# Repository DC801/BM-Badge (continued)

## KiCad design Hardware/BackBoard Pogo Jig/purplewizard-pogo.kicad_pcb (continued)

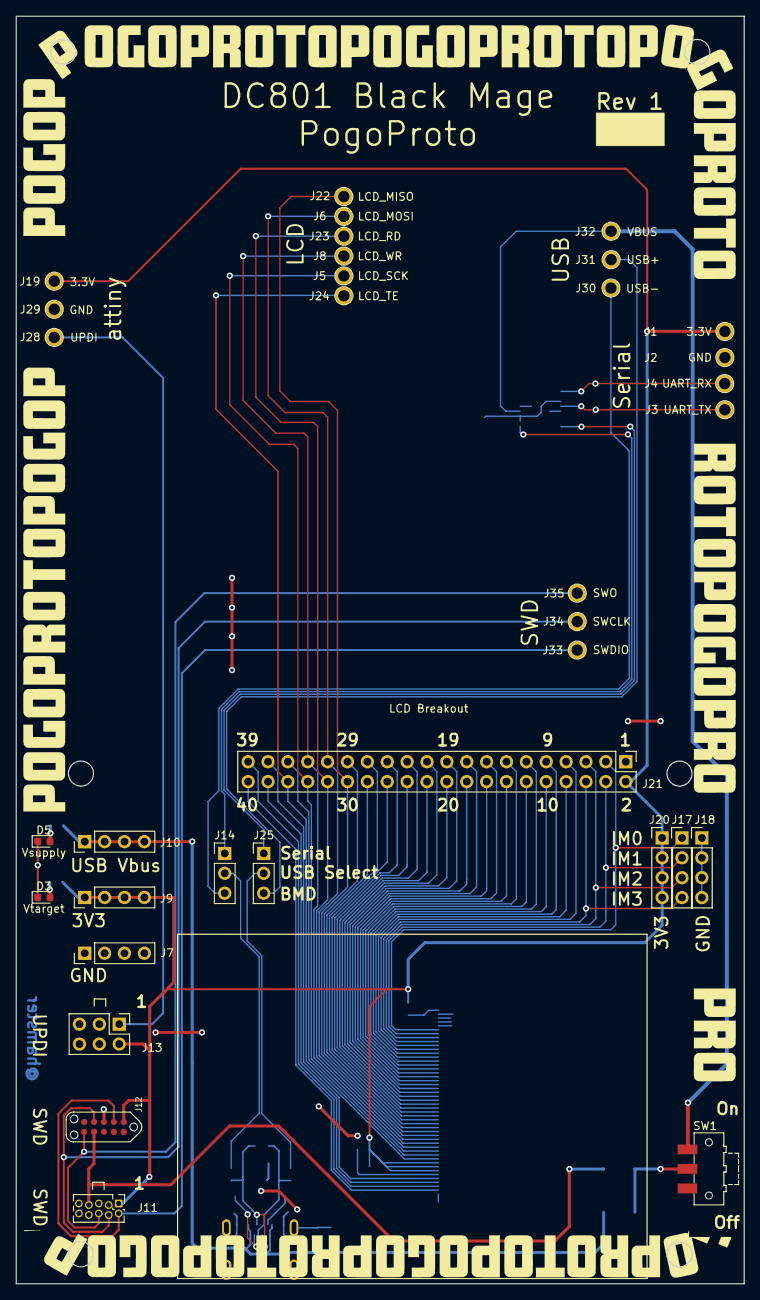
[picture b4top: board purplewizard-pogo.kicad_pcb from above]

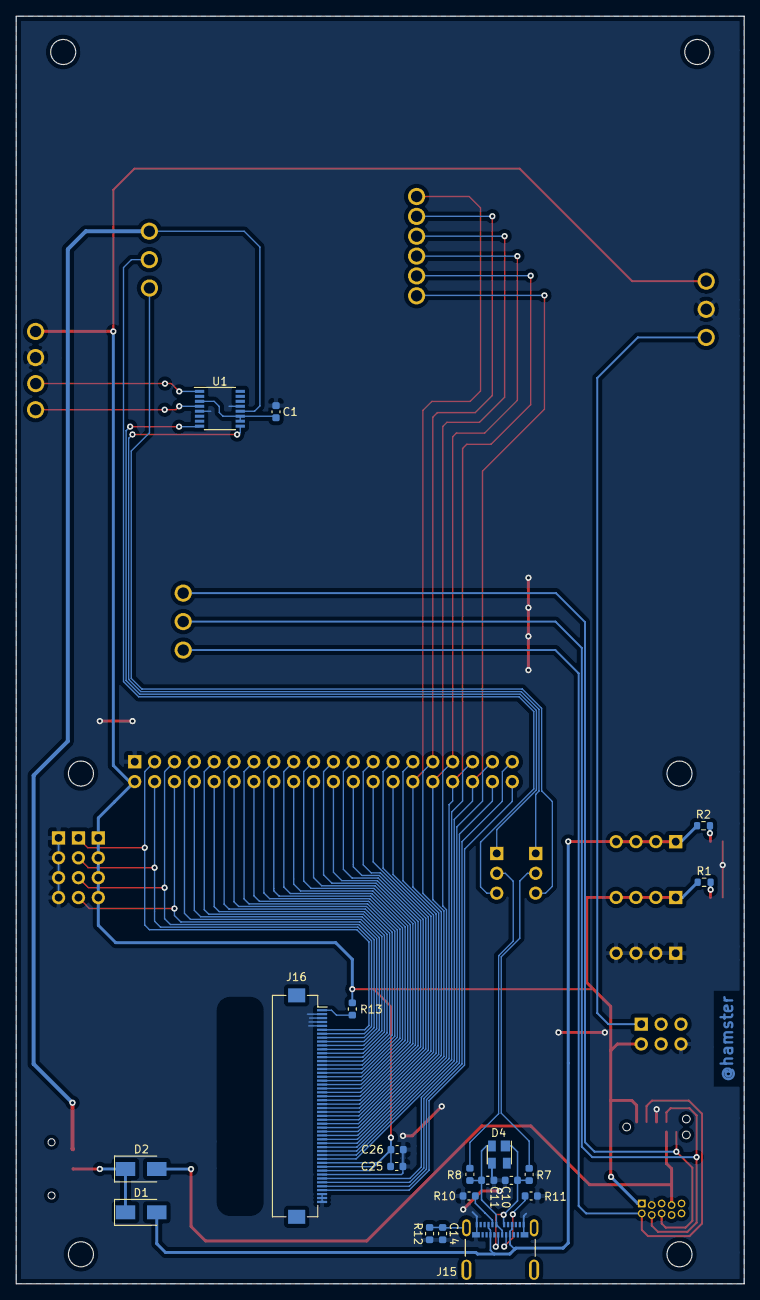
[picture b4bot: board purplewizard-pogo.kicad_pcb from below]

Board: 2 copper layers, 93.0 x 162.0 mm, 54 parts (20 on the bottom side), 65 nets.

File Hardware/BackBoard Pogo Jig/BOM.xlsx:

Ref Des | Description | Mfg Part # | Package | Supplier | Supplier Part # | QTY per badge | Cost ea | Cost badge
C1,C15,C25 | 0.1uF Cap |  | 0603 | Digikey | 478-06036C104KAT4ACT-ND | 3 | 1.78E-2 | 5.3400000000000003E-2
C10,C11 | 47pF Cap |  | 0603 | Digikey | 732-7750-1-ND | 2 | 2.3199999999999998E-2 | 4.6399999999999997E-2
C26 | 10uF cap |  | 0603 | Digikey | 587-6017-1-ND | 1 | 6.4399999999999999E-2 | 6.4399999999999999E-2
D1,D2 | Schottky diode | VS-10MQ040-M3/5AT |  | Digikey | 112-VS-10MQ040-M3/5ATDKR-ND | 2 | 0.12972 | 0.25944
D3,D5 | LEDs |  | 0603 | Digikey | 160-1435-1-ND | 2 | 8.4599999999999995E-2 | 0.16919999999999999
D4 | TVS Diode | SP0503BAHTG | SOT-143-4 | Digikey | F2715DKR-ND | 1 | 0.4622 | 0.4622
DNS | 2.4" TFT 320x240 LCD display |  |  | buydisplay | https://www.buydisplay.com/color-2-4-inch-tft-lcd-module-dis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 | 1 | 4.82 | 4.82
J15 | USB-C | 1054500101 |  | Digikey | WM12856CT-ND | 1 | 1.8717999999999999 | 1.8717999999999999
J16 | FPC connector | 62684-50210E9ALF | Top Contact, 50 pin | Digikey | 609-5388-1-ND | 1 | 0.82450000000000001 | 0.82450000000000001
R12 | 10k Resistor |  | 0603 | Digikey | RMCF0603JT10K0CT-ND | 2 | 5.5999999999999999E-3 | 1.12E-2
R10,R11 | 5.1k Resistor |  | 0603 | Digikey | RMCF0603JG5K10CT-ND | 2 |  | 0
R13 | 33R Resistor |  |  | Digikey | RMCF0603JT33R0CT-ND | 1 | 5.5999999999999999E-3 | 5.5999999999999999E-3
R1,R2 | 470R Resistor |  | 0603 | Digikey | RMCF0603JT470RCT-ND | 2 | 5.5999999999999999E-3 | 1.12E-2
R7,R8 | 27R Resistor |  | 0603 | Digikey | RMCF0603JT27R0CT-ND | 2 | 5.5999999999999999E-3 | 1.12E-2
SW1 | Power switch | JS102011SAQN |  | Digikey | 401-1999-1-ND | 1 | 0.50907999999999998 | 0.50907999999999998
J1, J19, J2, J22, J23, J24, J28, J29, J3, J30, J31, J32, J33, J34, J35, J4, J5,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 | Pogo Socket |  |  | Digikey | ED1012-ND | 19
 |  |  |  |  |  | Total Parts |  | Cost Per
 |  |  |  |  |  | 38 |  | 9.0198200000000028

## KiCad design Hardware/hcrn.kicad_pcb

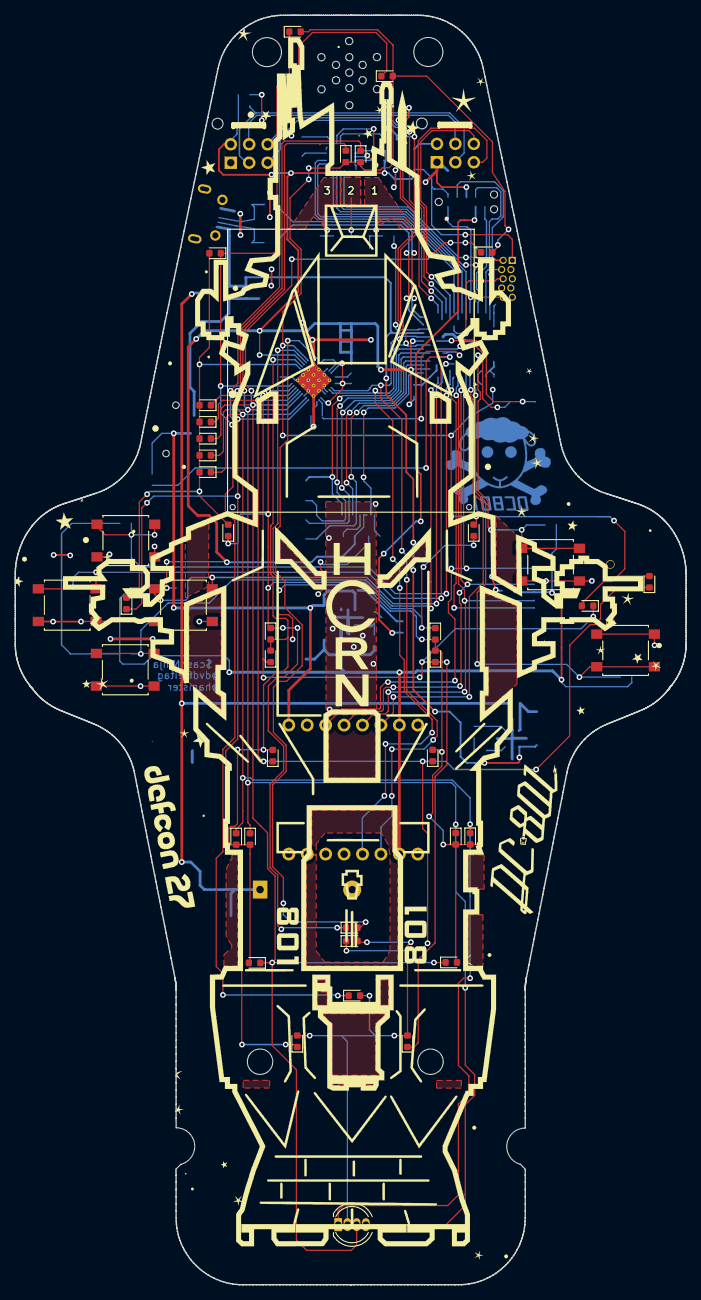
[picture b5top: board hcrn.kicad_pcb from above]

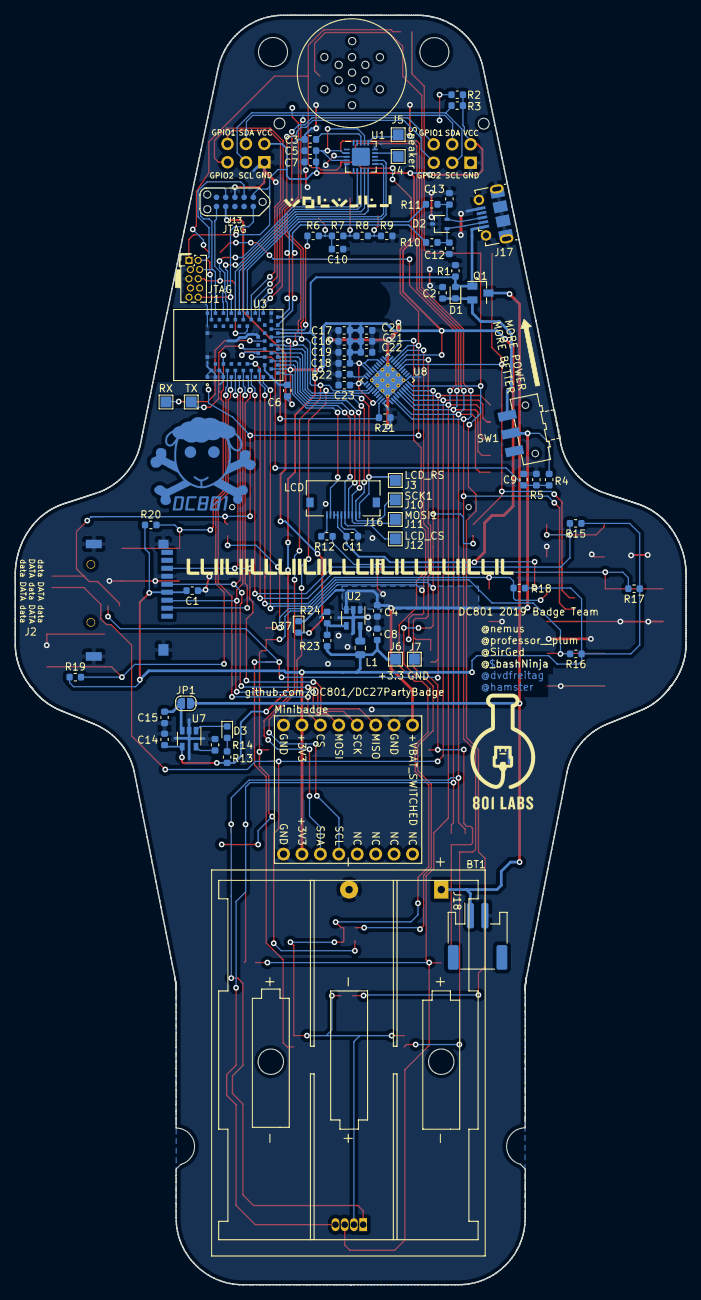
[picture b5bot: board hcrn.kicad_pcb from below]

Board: 2 copper layers, 92.5 x 175.0 mm, 120 parts (77 on the bottom side), 76 nets.

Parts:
BT1: Battery; BatteryHolder_Keystone_2479_3xAAA
C1, C2, C10, C11, C16, C18, C21: 0.1uF; C_0603_1608Metric
C3, C4, C5, C6, C7, C14, C15: 4.7uF; C_0603_1608Metric
C8, C20: 22uF; C_0603_1608Metric
C9: 1nF; C_0603_1608Metric
C12, C13: 47pF; C_0603_1608Metric
C17, C19, C22, C23: 0.47uF; C_0603_1608Metric
D1, D37: D_Schottky; D_0603_1608Metric
D2: SP0503BAHT; SOT-323_SC-70
D3: RED; LED_0603_1608Metric
D4, D5, D6, D7, D8, D9, D10, D11, D12, D13, D14, D15, D16, D17, D18, D19, D20, D21, D22, D23, D24, D25, D26, D27, D28, D29, D30, D31, D32, D33, D34, D35, D36: LED; LED_0603_1608Metric
D38: LED_ARGB; LED_D5.0mm-4_RGB
J1: JTAG; PinHeader_2x05_P1.27mm_Vertical_Sneaky
J2: Micro_SD_Card_SPI; MicroSD-Socket-Seeed-320090008
J3: LCD_RS; TestPoint_Pad_1.5x1.5mm
J4: SPKR+; TestPoint_Pad_1.5x1.5mm
J5: SPKR-; TestPoint_Pad_1.5x1.5mm
J6: 3.3V; TestPoint_Pad_1.5x1.5mm
J7: GND; TestPoint_Pad_1.5x1.5mm
J8: UART_TX; TestPoint_Pad_1.5x1.5mm
J9: UART_RX; TestPoint_Pad_1.5x1.5mm
J10: SCK1; TestPoint_Pad_1.5x1.5mm
J11: MOSI1; TestPoint_Pad_1.5x1.5mm
J12: LCD_CS; TestPoint_Pad_1.5x1.5mm
J13: TagConnect; TC2050-NL_SMALL
J16: LCD; XF2L-1035-1A
J17: USB_B_Micro; USB_Micro-B_Molex-105017-0001
J18: Battery; JST_PH_S2B-PH-SM4-TB_1x02-1MP_P2.00mm_Horizontal
JP1: LiPo Charger Enable; SolderJumper-2_P1.3mm_Open_RoundedPad1.0x1.5mm
L1: 4.7uH; L_0805_2012Metric
Q1: FDN360P; SuperSOT-3
R1, R7, R15, R16, R17, R18, R19, R20: 10k; R_0603_1608Metric
R2, R3: 4.7k; R_0603_1608Metric
R4: 806k; R_0603_1608Metric
R5: 2M; R_0603_1608Metric
R6: 3.9k; R_0603_1608Metric
R8: 15k; R_0603_1608Metric
R9: 4.99k; R_0603_1608Metric
R10, R11: 27R; R_0603_1608Metric
R12: 33R; R_0603_1608Metric
R13: 470R; R_0603_1608Metric
R14: 2.0k; R_0603_1608Metric
R21: 100k; R_0603_1608Metric
R22: 20k; R_0603_1608Metric
R23: 536k; R_0603_1608Metric
R24: 118k; R_0603_1608Metric
SW1: Power; SW_SPDT_CK-JS102011SAQN
SW2, SW3, SW4, SW5, SW6, SW7: SW_Push; SW_SPST_B3S-1000
U1: NAU8810; QFN-20-1EP_4x4mm_P0.5mm_EP2.5x2.5mm
U2: PAM2305DABADJ; SOT-23-5
U3: BMD-340; RIGADO_BMD-340
U4: Minibadge 1; SAINTCON-Minibadge-BackSilk
U5, U6: SHITTY_ADDON; Badgelife-SAOv169-BADGE-2x3-NoOutline
U7: MCP73832-2-OT; SOT-23-5
U8: IS31FL3736; QFN-40-1EP_5x5mm_P0.4mm_EP3.6x3.6mm_ThermalVias

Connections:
+3V3: C1.2, C5.2, C6.1, C7.2, C8.1, C11.2, C16.1, C17.2, C18.1, C19.2, C20.1, C21.1, C22.2, C23.1, J1.1, J2.4, J6.1, J13.1, J16.7, J16.8, L1.2, R2.2, R3.2, R15.1, R16.1, R17.1, R18.1, R19.1, R20.1, R23.2, U1.2, U1.4, U1.17, U3.17, U3.65, U4.7, U4.15, U5.1, U6.1, U8.17, U8.23, U8.27, U8.28, U8.31, U8.38
+BATT: BT1.1, J18.1, JP1.2, Q1.3
+BATT_SW: C4.1, D37.1, R4.2, R12.1, SW1.2, U2.1, U2.3, U4.1
/EE_Level1: C10.2, R6.2, R7.1
/EE_Level2: R7.2, R8.1
/EE_Level3: R8.2, R9.1
/USB+: R11.2, U3.68
/USB-: R10.2, U3.67
BUTTON_A: R19.2, SW6.1, U3.6
BUTTON_B: R20.2, SW7.1, U3.49
BUTTON_DOWN: R16.2, SW3.1, U3.15
BUTTON_LEFT: R17.2, SW4.1, U3.52
BUTTON_RIGHT: R18.2, SW5.1, U3.14
BUTTON_UP: R15.2, SW2.1, U3.12
EEPuzzle: R6.1, U3.27
GND: BT1.2, C1.1, C2.2, C3.1, C4.2, C5.1, C6.2, C7.1, C8.2, C9.2, C10.1, C11.1, C12.1, C13.2, C14.1, C15.1, C16.2, C17.1, C18.2, C19.1, C20.2, C21.2, C22.1, C23.2, D2.3, J1.3, J1.5, J2.6, J2.10, J7.1, J13.3, J16.6, J17.5, J17.6, J18.2, R1.1, R5.1, R9.2, R14.1, R21.1, R22.1, R24.1, SW2.2, SW3.2, SW4.2, SW5.2, SW6.2, SW7.2, U1.3, U1.5, U1.15, U2.2, U3.1, U3.2, U3.3, U3.4, U3.5, U3.16, U3.18, U3.29, U3.30, U3.45, U3.46, U3.47, U3.55, U4.2, U4.8, U4.16, U5.2, U6.2, U7.2, U8.4, U8.11, U8.26, U8.35, U8.36, U8.40, U8.41
I2S_LRCK: U1.8, U3.40
I2S_MCK: U1.10, U3.37
I2S_SCK: U1.9, U3.38
I2S_SCL: U1.11, U3.36
I2S_SDA: U1.12, U3.35
I2S_SDOUT: U1.7, U3.41
LCD_CS: J12.1, J16.5, U3.62
LCD_LED: J16.9, U3.61
LCD_RESET: J16.4, U3.19
LCD_RS: J3.1, J16.1, U3.64
LED_RESET: R21.2, U3.53, U8.39
MINI_CS: U3.7, U4.6
MISO0: J2.7, U3.8, U4.3
MOSI0: J2.3, U3.10, U4.5
MOSI1: J11.1, J16.3, U3.63
unnamed: C2.1, D1.1, Q1.2, SW1.3
unnamed: C3.2, U1.18
unnamed: C12.2, D2.1, J17.2, R10.1
unnamed: C13.1, D2.2, J17.3, R11.1
unnamed: C15.2, JP1.1, U7.3
unnamed: D3.1, U7.1
unnamed: D3.2, R13.2
unnamed: D10.1, D18.1, D34.1, U8.2
unnamed: D4.2, D5.2, D6.2, D7.2, D8.2, D9.2, D10.2, D11.2, U8.15
unnamed: D11.1, D35.1, D36.1, U8.10
unnamed: D4.1, D12.1, D19.1, D20.1, D28.1, U8.9
unnamed: D12.2, D13.2, D14.2, D15.2, D16.2, D17.2, U8.16
unnamed: D5.1, D13.1, D21.1, D26.1, D29.1, U8.8
unnamed: D6.1, D14.1, D22.1, D27.1, D30.1, U8.7
unnamed: D7.1, D15.1, D23.1, D31.1, D38.3, U8.6
unnamed: D8.1, D16.1, D24.1, D32.1, D38.4, U8.5
unnamed: D9.1, D17.1, D25.1, D33.1, D38.1, U8.3
unnamed: D18.2, D19.2, D26.2, D27.2, D36.2, D38.2, U8.21
unnamed: D20.2, D21.2, D22.2, D23.2, D24.2, D25.2, U8.18
unnamed: D28.2, D29.2, D30.2, D31.2, D32.2, D33.2, D34.2, D35.2, U8.19
unnamed: J4.1, U1.14
unnamed: J5.1, U1.16
unnamed: J16.10, R12.2
unnamed: L1.1, U2.5
unnamed: R14.2, U7.5
unnamed: R22.2, U8.30
unnamed: R23.1, R24.2, U2.4
S1_1: U3.31, U5.5
S1_2: U3.32, U5.6
S2_1: U3.34, U6.5
S2_2: U3.33, U6.6
SCK0: J2.5, U3.9, U4.4
SCK1: J10.1, J16.2, U3.21
SCL: R3.1, U3.23, U4.13, U5.4, U6.4, U8.34
SDA: R2.1, U3.25, U4.14, U5.3, U6.3, U8.33
SD_CS: J2.2, U3.11
SW0: J1.6, J13.6, U3.56
SWCLK: J1.4, J13.4, U3.43
SWDIO: J1.2, J13.2, U3.44
TC_PWR: D37.2, J13.7
UART_RX: J9.1, U3.24
UART_TX: J8.1, U3.22
VBAT_SENSE: C9.1, R4.1, R5.2, U3.20
VBUS: C14.2, D1.2, J17.1, Q1.1, R1.2, R13.1, U3.66, U7.4
nRESET: J1.10, J13.10, U3.39

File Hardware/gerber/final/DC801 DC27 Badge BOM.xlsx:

Refdes | Manufacturer | Part Number | Description | Package | Supplier | Supplier Part | Cost Each (assumes 100 unit pricing) | Qty per board | Stuff? | QOH | Needed | To Order | Cost Per Board | Qty ordered | Actual Cost | Datasheet
LiPo Charger |  |  |  |  |  |  |  |  |  |  | 10.0
D3 |  |  | Red LED, LiPo Charger | 0603 |  |  |  | 1.0 | N |  | 10
C14,C15 |  |  | 4.7uF, LiPo Charger | 0603 |  |  |  | 2.0 | N |  | 20
R14 |  |  | 2k ohm, LiPo Charger | 0603 |  |  |  | 1.0 | N |  | 10
R13 |  |  | 470 ohm, LiPo Charger | 0603 |  |  |  | 1.0 | N |  | 10
U7 | Microchip | MCP73832-2-OT | LiPo charger | SOT-23-5 |  |  |  | 1.0 | N |  | 10 |  |  |  |  | https://www.microchip.com/wwwproducts/en/MCP73832
J18 | JST | S2B-PH-SM4-TB(LF)(SN) | JST 2 pin |  | Digikey | 455-1749-1-ND |  | 1.0 |  | 50.0 | 10 | 0.0
Non-stuff, virtual |  |  |  |  |  |  |  |  |  |  | 0
J1 |  |  | JTAG | 2x5, 1.27mm |  |  |  |  | N |  | 0
J12 |  |  | JTAG | TC2050
J4-12 |  |  | Test point |  |  |  |  |  | N |  | 0
JP1 |  |  | Jumper pad |  |  |  |  |  | N |  | 0
U4 |  |  | Minibadge socket |  |  |  |  |  | N |  | 0
U5,U6 |  |  | Shitty addon |  |  |  |  |  | N |  | 0
Solder later |  |  |  |  |  |  |  |  |  |  | 0
BT1 | Keystone | 2479.0 | 3xAAA |  | Digikey | 36-2479-ND |  |  |  | 0.0 | 0
Speaker |  | SP-1504 | 8 ohm speaker |  | Digikey | 433-1106-ND |  |  |  | 0.0 | 0
D38 |  |  | RGB LED | RGB Through Hole | https://www.aliexpress.com/item/Free-shipping-100pcs-lot-5mm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 |  |  | 1.0 |  | 0.0 | 10 | 100.0
 |  |  |  |  |  |  |  |  |  |  | 0
Parts to stuff at board house |  |  |  |  |  |  |  |  |  |  | 0
C1,C2,C10,C11,C16,C18,C21 |  |  | 0.1uF 5v | 0603 | https://www.arrow.com/en/products/cl10b104kb8nnnc/samsung-el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 |  |  | 7.0 |  | 0.0 | 70 | 100.0
C3,C4,C5,C6,C7,C14,C15 |  |  | 4.7uF 5v | 0603 | https://www.arrow.com/en/products/cl10a475kp8nnnc/samsung-el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 |  |  | 7.0 |  | 50.0 | 70 | 100.0
C8,C20 |  |  | 22uF | 0603 | https://www.arrow.com/en/products/grm188r60j226me15d/murata-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 |  |  | 2.0 |  | 0.0 | 20 | 100.0
C9 |  |  | 1nF | 0603 | https://www.arrow.com/en/products/cl10b102mb8nnnc/samsung-el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 |  |  | 1.0 |  | 0.0 | 10 | 100.0
C12,C13 |  |  | 47pF | 0603 | https://www.arrow.com/en/products/cl10c470jb8nnnd/samsung-el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 |  |  | 2.0 |  | 0.0 | 20 | 100.0
C17,C19,C22,C23 |  |  | 0.47uF | 0603 | https://www.arrow.com/en/products/cl10b474kp8nnnc/samsung-el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 |  |  | 4.0 |  | 0.0 | 40 | 100.0
D1.D37 |  |  | Schottky | SOT-143 |  |  |  | 1.0 |  | 25.0 | 10 | 0.0
D2 | Littel Fuse | SP0503BAHT | TVS diode | SOT-143 | https://www.arrow.com/en/products/sp0503bahtg/littelfuse |  |  | 1.0 |  | 0.0 | 10 | 100.0
D30 |  |  | LED, white |  |  |  |  | 1.0 |  | 0.0 | 10 | 100.0
D33,D13,D21,D17,D25,D19,D36 |  |  | LED, purple |  |  |  |  | 7.0 |  | 0.0 | 70 | 100.0
D32,D10,D4,D28,D12,D20,D29,D14,D22,D16,D24,D15,D23,D27,D18,D26 |  |  | LED, amber |  |  |  |  | 16.0 |  | 0.0 | 160 | 250.0
D5,D6,D7,D8,D9,D11,D31,D34,D35 |  |  | LED, red | 0603 |  |  |  | 9.0 |  | 0.0 | 90 | 100.0
J2 | Schenzen Best | TF-01 | Micro SD Card Socket |  | https://www.aliexpress.com/item/10Pcs-TransFlash-TF-Micro-Me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 |  |  | 1.0 |  | 0.0 | 10 | 0.0 |  |  |  | https://statics3.seeedstudio.com/images/opl/datasheet/320090008.pdf
J16 |  | XF2L-1035-1A | FFC/FPC LCD connector |  | Digikey | Z5306CT-ND |  | 1.0 |  | 30.0 | 10 | 0.0
J17 | Molex | 105017-0001 | USB Micro B, 'with holes' |  | Digikey | WM1399CT-ND |  | 1.0 |  | 25.0 | 10 | 0.0
L1 |  |  | 4.7uH | 0805 | https://www.arrow.com/en/products/aiml-0805hc-4r7m-t/abracon |  |  | 1.0 |  | 0.0 | 10 | 100.0
Q1 | On Semi | FDN360P | P-Mosfet | SuperSOT-3 | Mouser | 512-FDN360P |  | 1.0 |  | 30.0 | 10 | 0.0
R1,R7,R15,R16,R17,R18,R19,R20 |  |  | 10k ohm | 0603 | https://www.arrow.com/en/products/rc0603jr-1310kl/yageo |  |  | 8.0 |  | 0.0 | 80 | 100.0
R2,R3 |  |  | 4.7k ohm | 0603 | https://www.arrow.com/en/products/rc0603jr-134k7l/yageo |  |  | 2.0 |  | 0.0 | 20 | 100.0
R4 |  |  | 806k ohm | 0603 | https://www.arrow.com/en/products/rc0603fr-07806kl/yageo |  |  | 1.0 |  | 0.0 | 10 | 100.0
R5 |  |  | 2M ohm | 0603 | https://www.arrow.com/en/products/rc0603jr-072ml/yageo |  |  | 1.0 |  | 0.0 | 10 | 100.0
R6 |  |  | 3.9k ohm | 0603 | https://www.arrow.com/en/products/rc0603jr-073k9l/yageo |  |  | 1.0 |  | 0.0 | 10 | 100.0
R8 |  |  | 15k ohm | 0603 | https://www.arrow.com/en/products/rc0603jr-0715kl/yageo |  |  | 1.0 |  | 0.0 | 10 | 100.0
R9 |  |  | 4.99k ohm | 0603 | https://www.arrow.com/en/products/nrc06f4991trf/nic-components |  |  | 1.0 |  | 0.0 | 10 | 100.0
R10,R11 |  |  | 27 ohm | 0603 | https://www.arrow.com/en/products/rc0603jr-0727rl/yageo |  |  | 2.0 |  | 0.0 | 20 | 100.0
R12 |  |  | 33 ohm | 0603 | https://www.arrow.com/en/products/rc0603fr-1333rl/yageo |  |  | 1.0 |  | 0.0 | 10 | 100.0
R21 |  |  | 100k | 0603 | https://www.arrow.com/en/products/rmcf0603jg100k/stackpole-e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 |  |  | 1.0 |  | 0.0 | 10 | 100.0
R22 |  |  | 20k | 0603 | https://www.arrow.com/en/products/rc0603jr-0720kl/yageo |  |  | 1.0 |  | 0.0 | 10 | 100.0
R23 |  |  | 536k 1% | 0603
R24 |  |  | 118k 1% | 0603
SW1 | CK | JS102011SAQN | Switch, SPDT |  |  |  |  | 1.0 |  | 8.0 | 10 | 2.0
SW2,SW3,SW4,SW5,SW6,SW7 |  | PTS645SM43SMTR92 LFS | SPST momentary |  | https://www.arrow.com/en/products/js102011saqn/ck |  |  | 6.0 |  | 100.0 | 60 | 0.0
U1 |  | NAU8810 | Audio codec | QFN-20 |  |  |  | 1.0 |  | 0.0 | 10 | 20.0
U2 |  | PAM2305DABADJ | Switching regulator, 3.3v | SOT-23-5 | https://www.arrow.com/en/products/pam2305dabadj/diodes-incorporated |  |  | 1.0 |  | 0.0 | 10 | 20.0
U3 | Rigado | BMD340 |  |  | Bender |  | 6.86 | 1.0 | Y | 400.0 | 10 | 0.0
U8 | ISSI | IS31FL3736 | LED Driver chip | QFN-40 |  |  |  | 1.0 |  | 0.0 | 10 | 20.0 |  |  |  | http://www.issi.com/WW/pdf/31FL3736.pdf

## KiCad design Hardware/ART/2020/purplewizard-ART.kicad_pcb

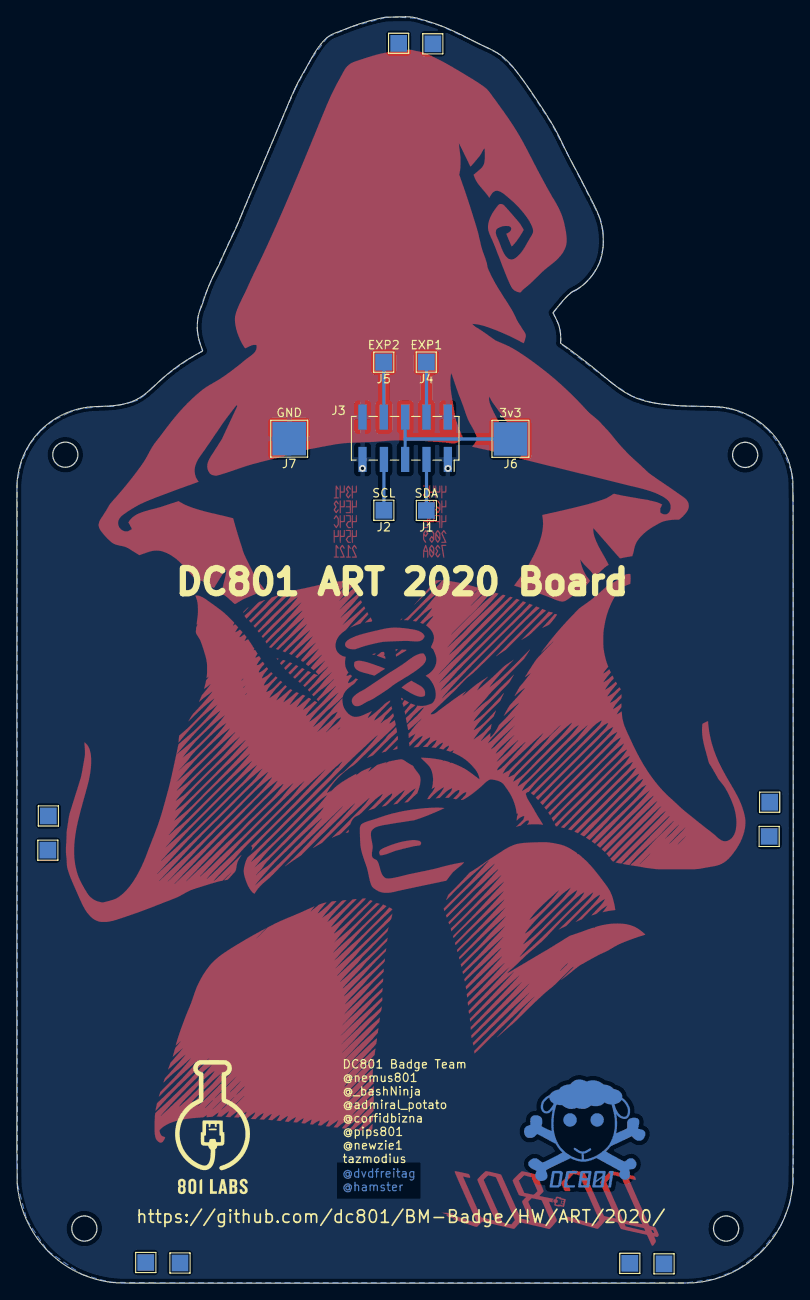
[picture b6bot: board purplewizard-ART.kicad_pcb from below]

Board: 2 copper layers, 92.5 x 151.0 mm, 7 parts (7 on the bottom side), 6 nets.

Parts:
J1: SDA; TestPoint_Pad_2.0x2.0mm
J2: SCL; TestPoint_Pad_2.0x2.0mm
J3: ART Expansion; PinSocket_2x05_P2.54mm_Vertical_SMD
J4: EXP1; TestPoint_Pad_2.0x2.0mm
J5: EXP2; TestPoint_Pad_2.0x2.0mm
J6: 3v3; TestPoint_Pad_4.0x4.0mm
J7: GND; TestPoint_Pad_4.0x4.0mm

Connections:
+3V3: J3.5, J3.6, J6.1
GND: J3.1, J3.2, J3.9, J3.10, J7.1
unnamed: J1.1, J3.3
unnamed: J2.1, J3.7
unnamed: J3.4, J4.1
unnamed: J3.8, J5.1

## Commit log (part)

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2024-04-07 add missing CSS classes of the component name to components
2024-04-07 less blue color for warnings
2024-04-08 use v-cloak to stop components from briefly flashing at first
2024-04-08 minor grammar: make folder input say Choose folder
2024-04-08 getting closer to automatic fixes
2024-04-08 minor: formatting
2024-04-13 change editor-accordion to use v-show instead of v-if
2024-04-14 Prelim ch2 credits
2024-04-14 USB dungeon debris aren't blockouts anymore.
2024-04-14 just use 'ch2' for the initial script names and let people delete it if they want
2024-04-15 remove short string-only entries in maps.json
2024-04-16 slightly reorganize editor-warning component
2024-04-16 remove index-debug.html as it's more useful non-committed (big)
2024-04-19 another css thing
2024-04-21 Added jukebox, stereo; other graphic tweaks
2024-04-21 Server rack graphics.
2024-04-21 Un-overwrote part of the debris graphics x_x
2024-04-21 start adding the mini rake goose quest
2024-04-23 add missing name props to Vue component definitions
2024-04-23 found one more double equals
2024-04-25 FPS counter + sleep to reduce CPU
2024-04-26 Graphics for workshop set (room 21)
2024-04-27 working unique generated script names with vuex
2024-04-28 Minor dialog + graphics improvements
2024-04-28 Bug fixes; easier Hanoi puzzle
2024-04-30 update notes
2024-04-30 remove deprecated bootstrap class has-danger
2024-05-04 Fix reset, rename EngineWindowFrame->DesktopWindowOutput
2024-05-05 More TODO goals
2024-05-08 Fixed the dungeon interior colors (might be some visual bugs ¬_¬)
2024-05-11 Portraits for more NPCs
2024-05-19 fix regression where errors showed in console but not GUI
2024-05-19 Rocco choreography improvements
2024-05-24 Fixing some stupid bugs
2024-05-26 Choreography and text improvements
2024-05-27 Remove ScreenManager after re-integrating to FrameBuffer
2024-06-02 Post-credits cutscene (and aftermath)
2024-06-16 Cutscene: Beatrice and Delmar reconciliation
2024-06-16 Web Build: Move File/USB/HAX lights, add frame icons
2024-06-23 Remaining King Gibson choreography + goldfish acquisition cutscene
2024-06-23 Use new CH2 menu, Fix CH2 DC801 Bling colors
    - Fix `mage_dat.ksy` out of date engine version
    - Fix an off by 1 error in image color palette validation
2024-07-04 Cleanup merge and get building again
2024-07-09 Bob's club on_tick bug fix + text improvements
2024-07-11 Soldering no longer involves terminal
2024-07-14 Text improvements (some from playtestting)
2024-07-21 Ch2 Main Menu Mage goes harder
2024-07-22 Post credits cutscene done + "dungeon" references removed (now "castle")
2024-07-26 More cleanup
    - remove references to DC801_DESKTOP, use DC801_EMBEDDED as control
    - fix circular reference between scriptControl and commandControl
    - remove unused actions
    - remove unused files
    - remove extra lines and parenthesis/inverted logic/etc
    - remove chunks of commented-out code
2024-07-27 Added mew menu animation screens to bling mode (DC801 showcase)
2024-07-28 Add the Goose mini rake quest
2024-07-28 Add Ch2 "Serial Terminal" artifact to Bling Mode
2024-07-30 Moved post credits scene to pre credits
2024-07-31 Fix rendering
2024-07-31 Text tuning + auto Bert secret cutscene part 3
2024-08-01 Artifact hero animation during intro cutscene + text polish
2024-08-01 More of the TODO text is gone.
2024-08-02 Security update for documentation generation
2024-08-02 Docs updates
2024-08-03 "Cutbug" debugger test
2024-08-03 Goose facts
2024-08-04 finish the two easter eggs, make them hidden commands
2024-08-04 Main Menu text updated to "Part 1 & Part 2"
2024-08-04 Ch2 credits
2024-08-06 Update README for ch2
2024-09-10 Switch to laptop
2024-11-12 Cleanup and debugging.
    * Fixed use of `|` instead of `&` in mage_geometry.cpp
    * Work on handling drawing geometry on top of the level in mage_map.cpp
    * FrameBuffer cleanup and consistency alignment for screen vs world coords
    * Removed read access to offset in EngineROM.h
2024-12-14 Bump nanoid in /SD_Card/MAGE/editor/dependencies/natlang-parser
    Bumps [nanoid](https://github.com/ai/nanoid) from 3.3.6 to 3.3.8.
    - [Release notes](https://github.com/ai/nanoid/releases)
    - [Changelog](https://github.com/ai/nanoid/blob/main/CHANGELOG.md)
    - [Commits](https://github.com/ai/nanoid/compare/3.3.6...3.3.8)
    ---
    updated-dependencies:
2025-01-15 Experiments with mathlang
2025-01-15 Mathlang: captures and literals can now repeat or skip; fixed off by one
2025-01-16 Mathlang: values can be collected for autocomplete
2025-01-17 Mathlang: onMatch scripts now with their patterns
2025-01-18 Mathlang: dialogs
2025-01-18 Mathlang: captures and unused labels no longer stored backwards
2025-01-18 Mathlang: change `state` to `file`
2025-01-20 Mathlang: redoing tryBranch (with unit tests)
2025-01-21 Mathlang: generic error no longer halts everything else
2025-01-21 Mathlang: dialog settings + crawlState stack bug fix
2025-01-22 Mathlang: serial dialog definitions
2025-01-22 Mathlang: script definitions
2025-01-23 Mathlang: show dialog block
2025-01-23 Mathlang: dialog literals
2025-01-24 Mathlang: Helper functions for common onEnd/onStart behaviors
2025-01-25 Mathlang: refactoring for better node printing and general file organization
2025-01-26 Mathlang: dialog unit tests; better unit test diff printing
2025-01-26 Mathlang: more unit tests, including some simple actions
2025-01-26 Mathlang: json literal unit test
2025-01-26 Mathlang: fixed bug: minus not checking for being double operator
2025-02-05 Mathlang: refinement involving lookups *
2025-02-06 Mathlang: better JSON literal error messaging, other refactoring
2025-02-08 Mathlang: include_macro unit tests
2025-02-09 Mathlang: unit tests for dialog definitions
2025-02-09 move suggested node version from 14 to 22 -- 14 won't work anymore on common Ubuntus, etc.
2025-02-09 Mathlang: a few more actions
2025-02-11 Mathlang: action with self/player/entity name
2025-02-24 move drawGeometry into call
2025-03-07 pip install compiledb without venv and change PATH modification to go in .bashrc
2025-03-07 update instructions for nrf-command-link-tools and jlink packages
2025-03-10 Revert "add linker option --allow-multiple-definition to common.make" (BAD IDEA)
    This reverts commit 986a38f0acf2ad7cdec1777c9e9dc2a014fe04c8.
2025-03-10 switch order of libm and libstdc++ for the linker, resolving multiple definition errors
2025-03-27 just use command names nrfjprog and mergehex in Makefile on linux, not full paths (verisons install to different places)
2025-08-17 Encoder: Remove NatLang, new TreeSitter parser incoming
2025-08-17 Fixing incongruities in geometry and scriptnames
2025-08-19 Fixed copy_script label suffix bug (leading to wrong jump indices); starting to update to more complex syntax
2025-08-19 Removed old natlang linker; try/catch for parser.setLanguage () since it fails sometimes
2025-08-19 copy_script now resembles a function call (instead of `copy!()`)
2025-08-20 Entities following player now take steps instead of gliding
2025-08-20 `===` and `!==` yields warnings, not syntax errors
2025-08-20 `f` now required in MathlangLocation
2025-08-21 Small cleanup for other stuff done today; methods for breaking if the thing isn't the class it should be
2025-08-24 Updating the build
2025-08-30 Bling maps no longer need a "Math" entity
2025-09-02 action_set_script can use "script literals" (≈lambdas) instead of a script name
    Same rules as `show dialog`: can be bare identifier, identifier and script block, or annonymous script block. The latter will get an auto-identifier name based on file/line/col.
    For things like this, the "comparison" tests will retain the original script name, but the "real" code will omit it.
    (Preparation for possible in-engine arrays)
2025-09-03 Excised common lambda behavior and break/continue handling; massive `parser-node.ts` cleanup
2025-09-04 Expression handling more uniform
2025-09-05 COPY_SCRIPT coerced to CopyMacro when from JSON literals; arbitrary JSON actions now allowed
    - ALL copied scripts now have a reference to the node they were "called" from
    - CopyMacro now handles search_and_replace instead of COPY_SCRIPT
    - JSON literal handling is done one action (object) at a time instead of as a whole array
    - JSON objects now made into Actions (or MathlangNodes) immediately
    - New UnknownAction class: for the time between the invention of a bytecode instruction and its implementation in mathlang
2025-09-06 Moving from `(f, node)` to `(debug)`: captures done, starting on actions
2025-09-06 Removed `mathlang` property on MathlangNodes (no longer used)
2025-09-07 Array experiments: creating with initial values
2025-09-07 `ARRAY_SLICE_BY_VARIABLE` and `ARRAY_SLICE_TWICE_BY_VARIABLE` work with mixed values
    Can use numbers, strings, and int expressions
2025-09-12 More modular, more realistic array method chains
2025-09-13 ArrayMap with lambda (fn defined in place)
2025-09-13 Moving some "file" unit tests to be "action" unit tests
2025-09-13 Setting up for generic mathlang error messages
2025-09-14 Arrays: Implement actions `[array_new,array_log, array_push_from_value]`
    - Serial: Move most debug logging into a public method that can also be used for sending messages to serial console from the scripting system
2025-09-21 (s)dialog definition duplication in fn call bug fix; preparing Hanoi/hamster scripts for arrays
2025-09-23 Mathlang nodes and Actions can tested for equality
2025-09-23 Script definitions in fn calls now baked separately
2025-09-28 Encoder: Silence excessively excessive logging
2025-10-02 Int expressions allowed in fn args
2025-10-02 Slight syntax polish (testing syntax)
2025-10-12 Can delete command fails
2025-10-12 Arrays: Implement action `array_read_from_variable_index_into_variable`
2025-10-12 Added optional semicolons to some script body items that lacked them
2025-10-19 Fixed overeager trailing comma detection panic
2025-10-26 Arrays: Implement actions `array_write_into_[index_from_value, index_from_variable, variable_index_from_value, variable_index_from_variable]`
2025-11-09 Mouse (cursor) test room
2025-11-16 Making a bunch of new red squiggles go away
2026-01-11 Fixed: Array slice missing `array` when printing from bytecode
2026-01-11 Fix: actually making the new temp array; unit test improvements
2026-01-11 A few more array unit tests
2026-01-11 Follower array now a double-ended queue
2026-01-11 Array read OOB unit test
2026-01-13 Quick "double follower" proof of concept
2026-01-25 Plates of Hanoi now 100% arrays (and 0% array emulation)
2026-01-25 Arrays: Fix negative numbers and OutOfBounds lookups
2026-02-01 Followers now more generic
    - Read/write position offset based on sprite size (select entities)
    - Following queues can be made for generic follower and followee
2026-02-01 Scooted Y of followers up 1 px
2026-03-15 Array map unit tests pass, first try
2026-03-22 Goose train (new follower proof of concept)
    This version has three entities following the player with unique timing and spacing, meaning the followers need not know who the other followers are. Followers may clump up, but this is more charming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
2026-03-29 Unit test for cursor teleportation bug
    - An on_tick that teleports an entity to the player seems to keep running for 1 tick after being cleared
2026-04-05 `ARRAY_RENAME` param names update
2026-04-19 Actions: Implement `array_rename, set_player_entity`
    - Fix reading values from deleted arrays / invalid indices
2026-04-20 `ARRAY_RENAME` implemented in MGS
2026-04-20 `SET_PLAYER_ENTITY` implemented in MGS
2026-04-26 Small template string optimization for follower fns
